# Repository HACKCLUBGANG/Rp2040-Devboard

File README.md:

# Rp2040-Devboard
This is a rp2040 chip powered devliopment board with alot  of  gpio pins to  control different modules
It has usb  c, flash  memory, onboard led, 40 total pins, rp2040 microcontroller
It can be easily used in projects.

# How
The rp2040  reads  the flash memory and runs the code given on it and performs tasks written in the code.
The  cystal oscillator proivides clock signals.
The usb c  is connected  a device which  can upload code to  the devlopment board

# Images

3d PCB Design

https://github.com/user-attachments/assets/56b6413a-4eb3-4e2f-bcef-c29688b946a8

PCB 

Schematic

# Programming

The RP2040 can be programmed using appslike aduino ide etc.

# BOM 

# VIBRIS – Bill of Materials (BOM)

| **Component Name** | **Quantity** | **Product Link** | **Price (USD / Unit)** |
| :--- | :---: | :--- | :---: |
| RP2040 Microcontroller (LQFN-56) | 1 | [LCSC C2040](https://www.lcsc.com/product-detail/C2040.html) | $0.9975 |
| USB-C Receptacle (TYPE-C-31-M-12, 16P) | 1 | [LCSC C165948](https://www.lcsc.com/product-detail/C165948.html) | $0.1724 |
| NCP1117-3.3 Voltage Regulator (SOT-223) | 1 | [LCSC C26537](https://www.lcsc.com/product-detail/C26537.html) | $0.2344 |
| 10µF Ceramic Capacitor (1206, X5R, 50V) | 2 | [LCSC C13585](https://www.lcsc.com/product-detail/C13585.html) | $0.2683 |
| 0.1µF (100nF) Ceramic Capacitor (0402, X7R, 16V) | 13 | [LCSC C1525](https://www.lcsc.com/product-detail/C1525.html) | $0.0029 |
| 33pF Ceramic Capacitor (0402, C0G, 50V) | 2 | [LCSC C466229](https://www.lcsc.com/product-detail/C466229.html) | $0.0033 |
| 12MHz Crystal | 1 | [LCSC C5455760](https://www.lcsc.com/product-detail/C5455760.html) | Verify |
| Blue SMD LED (1206) | 1 | [LCSC C28310438](https://www.lcsc.com/product-detail/C28310438.html) | $0.0158 |
| 330Ω SMD Resistor (1206) | 1 | [LCSC C4188684](https://www.lcsc.com/product-detail/C4188684.html) | Verify |
| 5.1kΩ SMD Resistor (USB-C CC1/CC2 Pull-ups) | 2 | [LCSC C25905](https://www.lcsc.com/product-detail/C25905.html) | $0.0023 |
| 1kΩ SMD Resistor (0402) | 2 | [LCSC C106235](https://www.lcsc.com/product-detail/C106235.html) | $0.0041 |
| 10kΩ SMD Resistor (0402) | 1 | [LCSC C60490](https://www.lcsc.com/product-detail/C60490.html) | $0.0038 |
| 27Ω SMD Resistor (0402) | 2 | [LCSC C25100](https://www.lcsc.com/product-detail/C25100.html) | $0.0013 |
| **Total Components** | **30** | | |

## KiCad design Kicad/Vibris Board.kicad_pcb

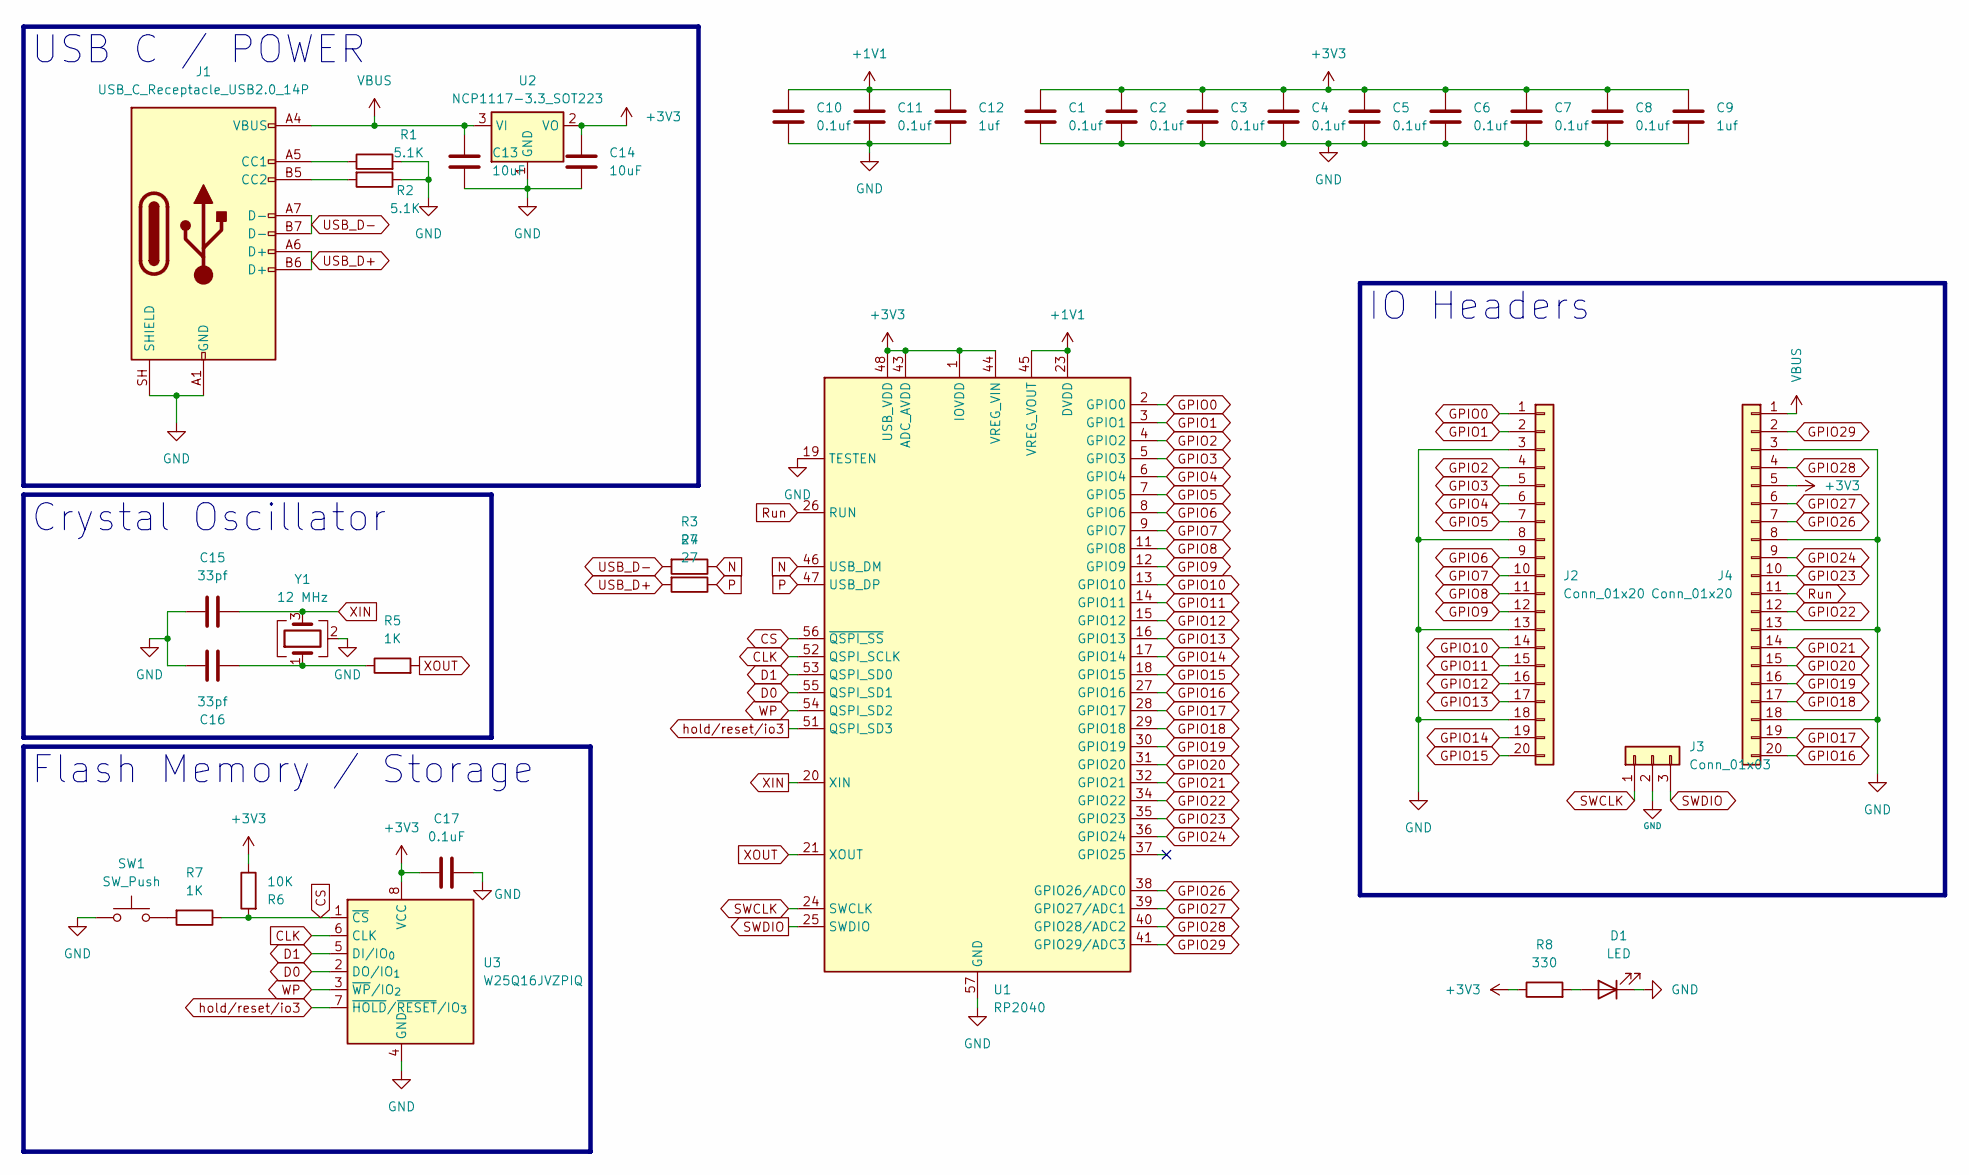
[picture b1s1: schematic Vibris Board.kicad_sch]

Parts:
C1, C2, C3, C4, C5, C6, C7, C8, C10, C11: 0.1uf; C_0402_1005Metric
C9, C12: 1uf; C_0603_1608Metric
C13, C14: 10uF; C_0603_1608Metric
C15, C16: 33pf; C_0805_2012Metric
C17: 0.1uF; C_0402_1005Metric
D1: LED; LED_0603_1608Metric
J1: USB_C_Receptacle_USB2.0_14P; USB_C_Receptacle_HRO_TYPE-C-31-M-12
J2, J4: Conn_01x20; PinHeader_1x20_P2.54mm_Vertical
J3: Conn_01x03; PinHeader_1x03_P2.54mm_Vertical
R1, R2: 5.1K; R_0402_1005Metric
R3, R4: 27; R_0402_1005Metric
R5, R7: 1K; R_0402_1005Metric
R6: 10K; R_0402_1005Metric
R8: 330; R_0603_1608Metric
SW1: SW_Push; SW_Push_SPST_NO_Alps_SKRK
U1: RP2040; QFN-56-1EP_7x7mm_P0.4mm_EP3.2x3.2mm
U2: NCP1117-3.3_SOT223; SOT-23
U3: W25Q16JVZPIQ; Winbond_USON-8-1EP_3x2mm_P0.5mm_EP0.2x1.6mm
Y1: 12 MHz; Crystal_SMD_3225-4Pin_3.2x2.5mm

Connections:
+1V1: C10.1, C11.1, C12.1, U1.23 (DVDD), U1.45 (VREG_VOUT), U1.50 (DVDD)
+3V3: C1.1, C2.1, C3.1, C4.1, C5.1, C6.1, C7.1, C8.1, C9.1, C14.1, C17.1, J4.5, R6.1, R8.1, U1.1 (IOVDD), U1.10 (IOVDD), U1.22 (IOVDD), U1.33 (IOVDD), U1.42 (IOVDD), U1.43 (ADC_AVDD), U1.44 (VREG_VIN), U1.48 (USB_VDD), U1.49 (IOVDD), U2.2 (VO), U3.8 (VCC)
CLK: U1.52 (QSPI_SCLK), U3.6 (CLK)
CS: R6.2, R7.1, U1.56 (~QSPI_SS), U3.1 (~CS)
D0: U1.55 (QSPI_SD1), U3.2 (DO/IO_{1})
D1: U1.53 (QSPI_SD0), U3.5 (DI/IO_{0})
GND: C1.2, C2.2, C3.2, C4.2, C5.2, C6.2, C7.2, C8.2, C9.2, C10.2, C11.2, C12.2, C13.2, C14.2, C15.1, C16.1, C17.2, D1.1 (K), J1.A1 (GND), J1.A12 (GND), J1.B1 (GND), J1.B12 (GND), J1.SH (SHIELD), J2.3, J2.8, J2.13, J2.18, J3.2, J4.3, J4.8, J4.13, J4.18, R1.2, R2.1, SW1.1, U1.19 (TESTEN), U1.57 (GND), U2.1 (GND), U3.4 (GND), Y1.2 (G), Y1.4 (G)
GPIO0: J2.1, U1.2 (GPIO0)
GPIO1: J2.2, U1.3 (GPIO1)
GPIO2: J2.4, U1.4 (GPIO2)
GPIO3: J2.5, U1.5 (GPIO3)
GPIO4: J2.6, U1.6 (GPIO4)
GPIO5: J2.7, U1.7 (GPIO5)
GPIO6: J2.9, U1.8 (GPIO6)
GPIO7: J2.10, U1.9 (GPIO7)
GPIO8: J2.11, U1.11 (GPIO8)
GPIO9: J2.12, U1.12 (GPIO9)
GPIO10: J2.14, U1.13 (GPIO10)
GPIO11: J2.15, U1.14 (GPIO11)
GPIO12: J2.16, U1.15 (GPIO12)
GPIO13: J2.17, U1.16 (GPIO13)
GPIO14: J2.19, U1.17 (GPIO14)
GPIO15: J2.20, U1.18 (GPIO15)
GPIO16: J4.20, U1.27 (GPIO16)
GPIO17: J4.19, U1.28 (GPIO17)
GPIO18: J4.17, U1.29 (GPIO18)
GPIO19: J4.16, U1.30 (GPIO19)
GPIO20: J4.15, U1.31 (GPIO20)
GPIO21: J4.14, U1.32 (GPIO21)
GPIO22: J4.12, U1.34 (GPIO22)
GPIO23: J4.10, U1.35 (GPIO23)
GPIO24: J4.9, U1.36 (GPIO24)
GPIO26: J4.7, U1.38 (GPIO26/ADC0)
GPIO27: J4.6, U1.39 (GPIO27/ADC1)
GPIO28: J4.4, U1.40 (GPIO28/ADC2)
GPIO29: J4.2, U1.41 (GPIO29/ADC3)
N: R3.1, U1.46 (USB_DM)
unnamed: C16.2, R5.1, Y1.1
unnamed: D1.2 (A), R8.2
unnamed: J1.A5 (CC1), R1.1
unnamed: J1.B5 (CC2), R2.2
unnamed: R7.2, SW1.2
P: R4.1, U1.47 (USB_DP)
Run: J4.11, U1.26 (RUN)
SWCLK: J3.1, U1.24 (SWCLK)
SWDIO: J3.3, U1.25 (SWDIO)
USB_D+: J1.A6 (D+), J1.B6 (D+), R4.2
USB_D-: J1.A7 (D-), J1.B7 (D-), R3.2
VBUS: C13.1, J1.A4 (VBUS), J1.A9 (VBUS), J1.B4 (VBUS), J1.B9 (VBUS), J4.1, U2.3 (VI)
WP: U1.54 (QSPI_SD2), U3.3 (~WP/IO_{2})
XIN: C15.2, U1.20 (XIN), Y1.3
XOUT: R5.2, U1.21 (XOUT)
hold/reset/io3: U1.51 (QSPI_SD3), U3.7 (~HOLD/~RESET/IO_{3})

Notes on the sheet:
USB C / POWER
Flash Memory / Storage
IO Headers
Crystal Oscillator

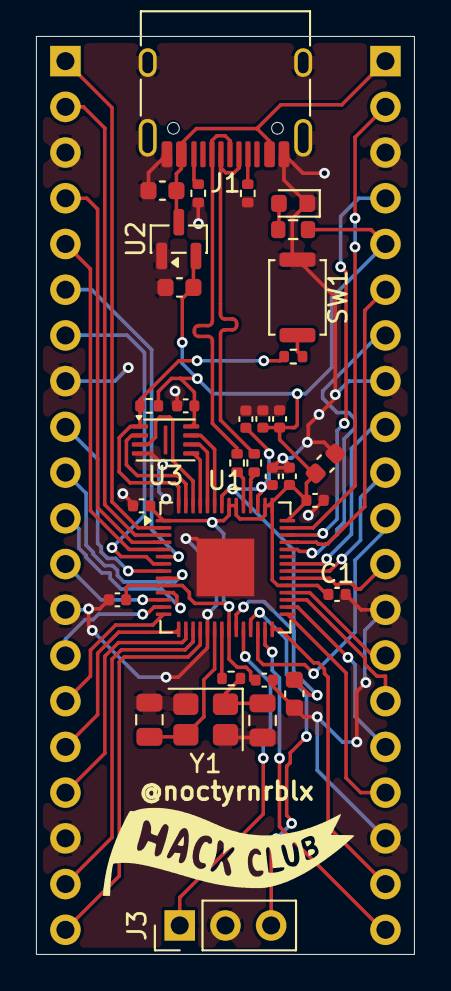
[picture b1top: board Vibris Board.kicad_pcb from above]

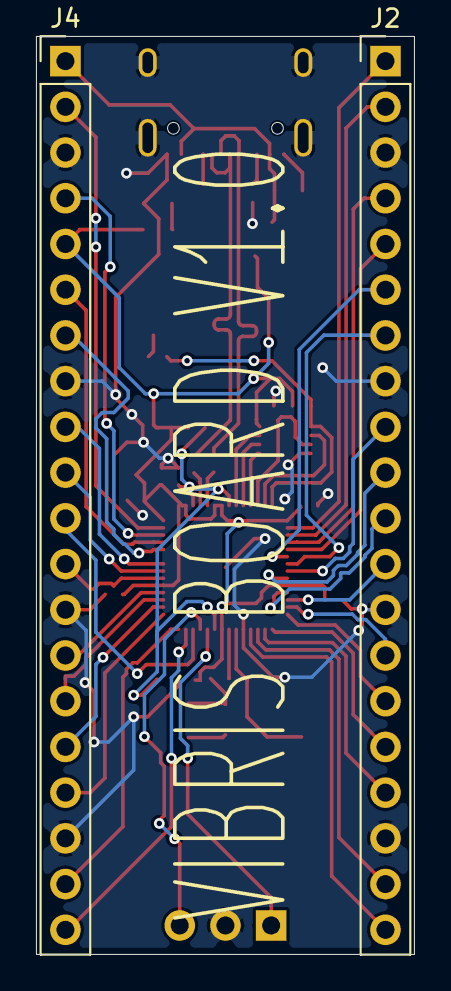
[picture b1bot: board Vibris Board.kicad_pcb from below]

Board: 2 copper layers, 21.0 x 51.0 mm, 35 parts (2 on the bottom side), 53 nets.
